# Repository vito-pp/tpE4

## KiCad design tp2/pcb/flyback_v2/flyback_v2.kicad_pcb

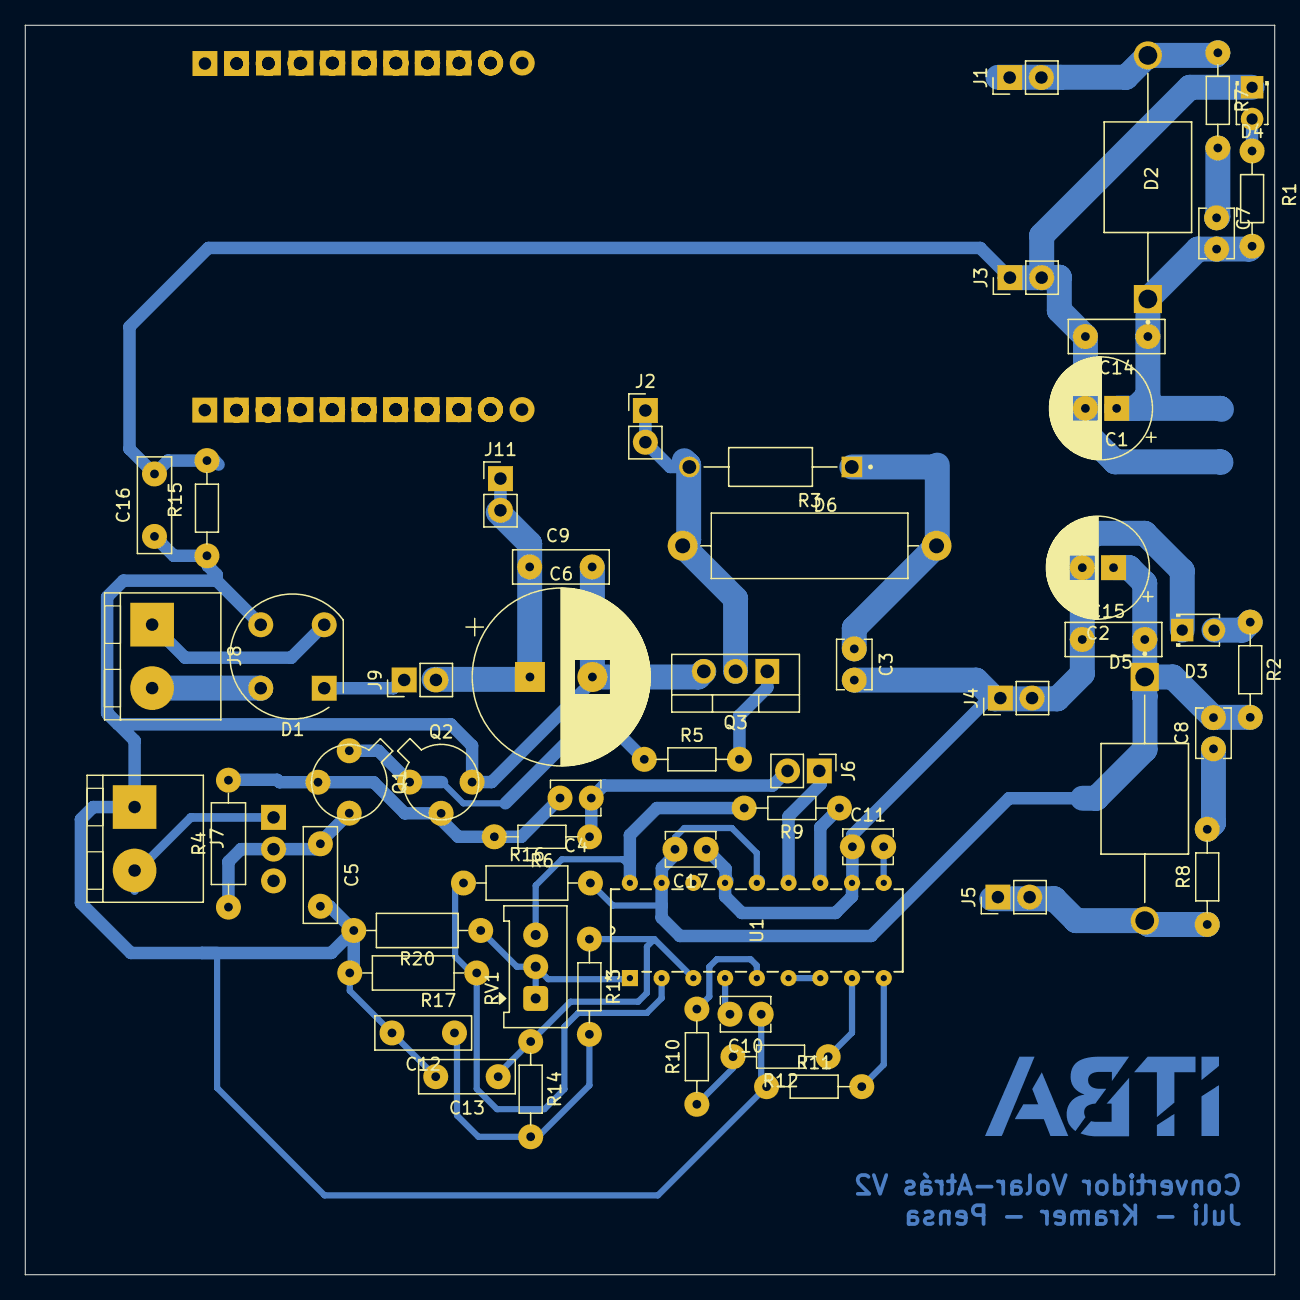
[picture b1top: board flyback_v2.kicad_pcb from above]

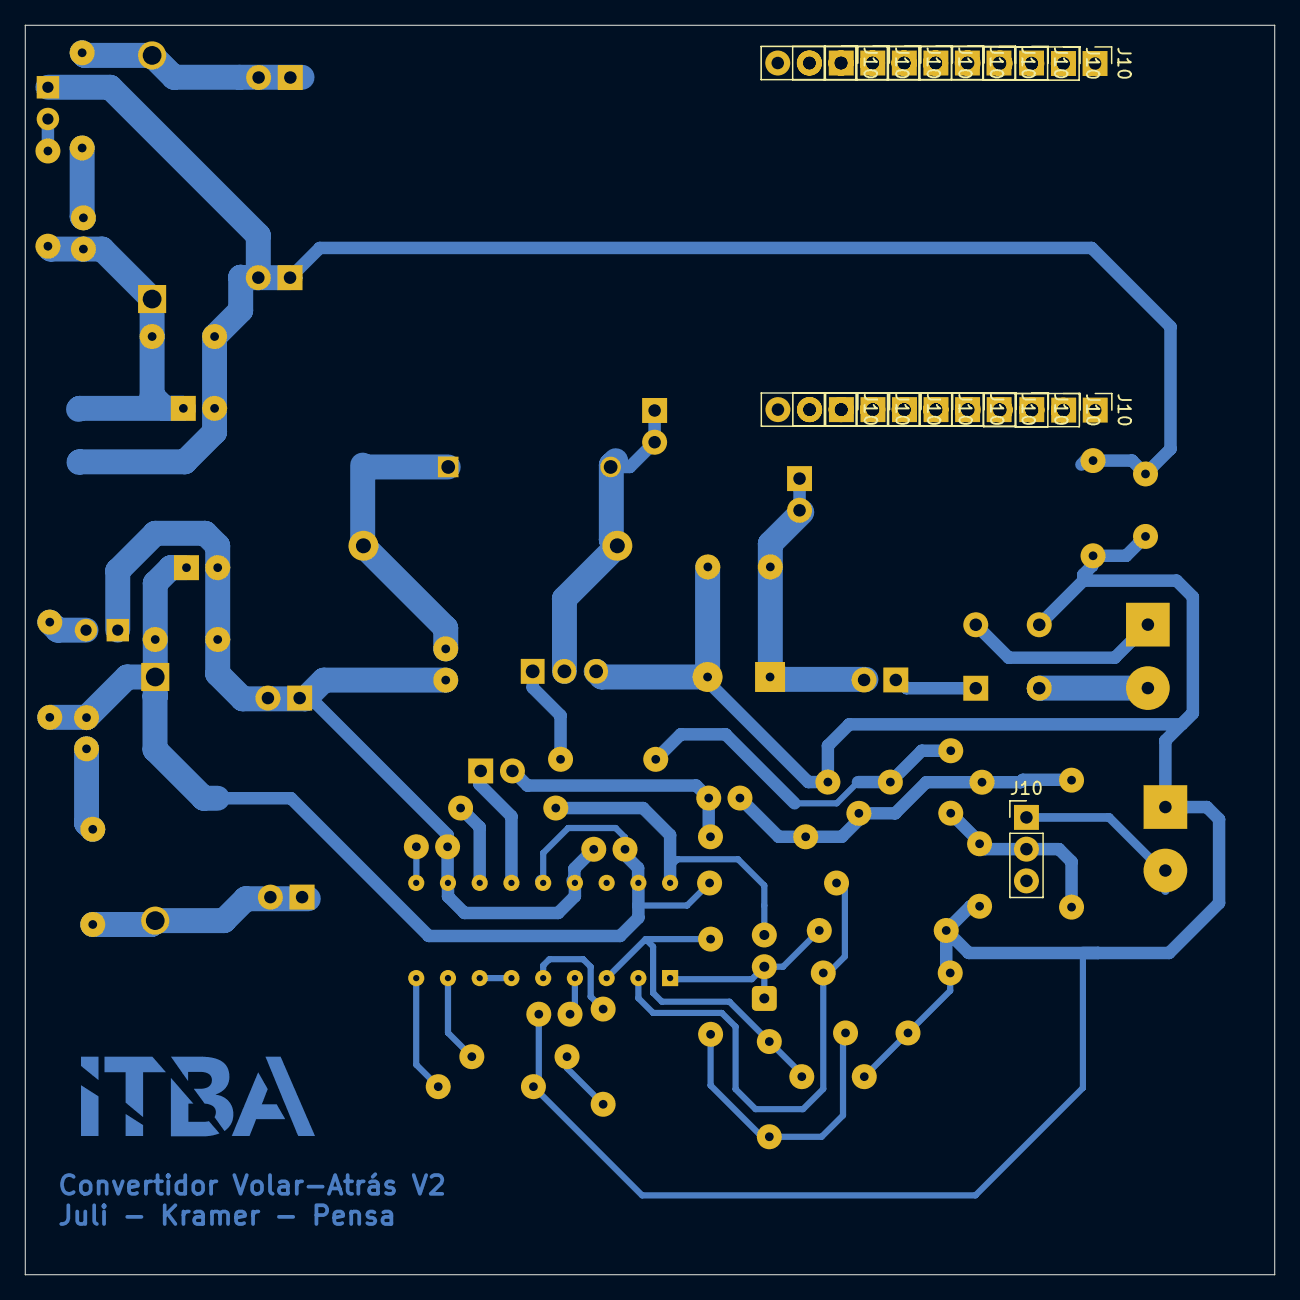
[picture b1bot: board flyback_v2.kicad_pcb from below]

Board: 2 copper layers, 100.0 x 100.0 mm, 75 parts (19 on the bottom side), 35 nets.

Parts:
C1, C2: 10u; CP_2.50mm
C3: 22p-800V; C_2.5mm
C4, C10, C11: 1n; C_2.5mm
C5, C14, C15: 1u; C_5mm
C6: 47u-400V; CP_5.00mm
C7, C8: C-50V; C_2.5mm
C9: 100n-400V; C_5mm
C12, C13: 47p; C_5mm
C16: 1n; C_5mm
C17: 100n; C_2.5mm
D1: W10M; Diode_Bridge_Round_D9.8mm
D2, D5: 6A20G; DIOAD1950W125L885D700
D3, D4: LED; LED_D1.8mm_W3.3mm_H2.4mm
D6: MUR160; DIOAD1300W80L670D310
J1, J2, J3, J4, J5, J6, J9, J11: Connector_2; PinHeader_1x02_P2.54mm_Vertical
J7, J8: Terminal_2; Bornera_2_P5mm
J10, J10#2, J10#3, J10#4, J10#5, J10#6, J10#7, J10#8, J10#9, J10#10, J10#11, J10#12, J10#13, J10#14, J10#15, J10#16, J10#17, J10#18, J10#19: Connector_3; PinHeader_1x03_P2.54mm_Vertical
Q1: 2N2222; TO-18-3
Q2: 2N2907; TO-18-3
Q3: TRBUZ80; TO-220-3_Vertical
R1: 1k2; R_0.125W
R2: 1k8; R_0.125W
R3: 56k-1W; R_1W
R4: 1k-0.25W; R_0.25W
R5: 22-0.125W; R_0.125W
R6: 470-0.125W; R_0.125W
R7, R8: R; R_0.125W
R9, R10, R12, R13, R14: 22k; R_0.125W
R11: 18k; R_0.125W
R15: 2Meg2; R_0.125W
R16, R20: 10k; R_0.25W
R17: 3k9; R_0.25W
RV1: 10k; RV_Preset_multivuelta_10mm_5mm
U1: UC3526AN; N18

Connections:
16V: J7.2, J10#5.1
GND: C2.2, C3.2, C5.2, C6.2, C9.2, C10.1, C11.1, C12.2, C13.2, C15.1, C16.1, C17.1, D1.3 (-), D3.1 (K), J4.1, J4.2, J7.1, Q2.3 (C), Q3.3 (S), R11.1, R15.1, R17.2, R20.2, U1.11 (RD), U1.15 (GROUND)
GNDREF: C1.2, C14.2, C16.2, D4.1 (K), J3.1, J3.2, R15.2
unnamed: C3.1, D6.C, R3.2
unnamed: C4.1, J6.2, R6.1
unnamed: C7.1, R7.2
unnamed: C8.1, R8.2
unnamed: C12.1, R13.2, R14.2
unnamed: D1.1 (+), J9.1
unnamed: D2.A, J1.1, J1.2, R7.1
unnamed: D3.2 (A), R2.1
unnamed: D4.2 (A), R1.2
unnamed: D5.A, J5.1, J5.2, R8.1
unnamed: C4.2, Q1.2 (B), Q2.2 (B), R4.2, R6.2
unnamed: Q1.1 (E), Q2.1 (E), R5.1
unnamed: Q3.1 (G), R5.2
unnamed: U1.6 (-CURRENT_SENSE), U1.7 (+CURRENT_SENSE)
unnamed: C13.1, R13.1, R14.1, U1.3 (COMP)
unnamed: C10.2, U1.4 (CSS)
unnamed: C11.2, U1.10 (CT)
unnamed: R10.2, U1.5 (RESET*)
unnamed: R11.2, U1.9 (RTIMING)
unnamed: R12.1, U1.8 (SHUTDOWN*)
unnamed: R9.1, U1.12 (SYNC*)
Vcol: C5.1, J10#5.2, Q1.3 (C), R4.1
Vcontrol: J6.1, U1.13 (OUTPUT_A)
Vdrain: D6.A, J2.1, J2.2, Q3.2 (D), R3.1
Vin: C6.1, C9.1, J9.2, J11.1, J11.2
Vlinea: D1.4, J8.2
Vneutro: D1.2, J8.1
Vout: C1.1, C7.2, C14.1, D2.C, R1.1
Vrealim: C2.1, C8.2, C15.2, C17.2, D5.C, J10#5.3, R2.2, R16.2, U1.14 (VC), U1.17 (+VIN)
Vrealim': R16.1, R17.1, U1.2 (-ERROR)
Vref: R9.2, R10.1, R12.2, RV1.3, U1.18 (VREF)
Vref': R20.1, RV1.1, RV1.2, U1.1 (+ERROR)

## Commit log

2025-10-08 first commit :^D
2025-10-08 removed copied /flyback
2025-10-08 added almost all footprints to pcb
2025-10-08 hay que routear
2025-10-08 hay que routear2
2025-10-08 rutea facu
2025-10-08 checkpoint antes de div res
2025-10-08 ya rutie la flybuk
2025-10-09 por si me muero
2025-10-09 listo el routeo
2025-10-09 listo el routeo2
2025-10-09 pcb quemado
2025-10-11 commit v2 sin disipador
2025-10-11 puse el jumper de Vrealim y 16V
2025-10-11 elimine pdf viejo del schem
2025-10-11 agregue datasheets y linkee un modelo 3d
2025-10-11 rute finished, + pnies trafo + pdf
2025-10-11 updated gitignore y agregue datasheet nucleo
2025-10-11 borre archivo basura
2025-10-13 datasheet nucleo
2025-10-13 agregue /output en /pcb
2025-10-22 agregue mediciones
2025-10-27 version final sch
2025-11-24 entrega tp2 y empece tp3
2025-11-24 arregle algo del simu
2025-11-28 para vos facu
